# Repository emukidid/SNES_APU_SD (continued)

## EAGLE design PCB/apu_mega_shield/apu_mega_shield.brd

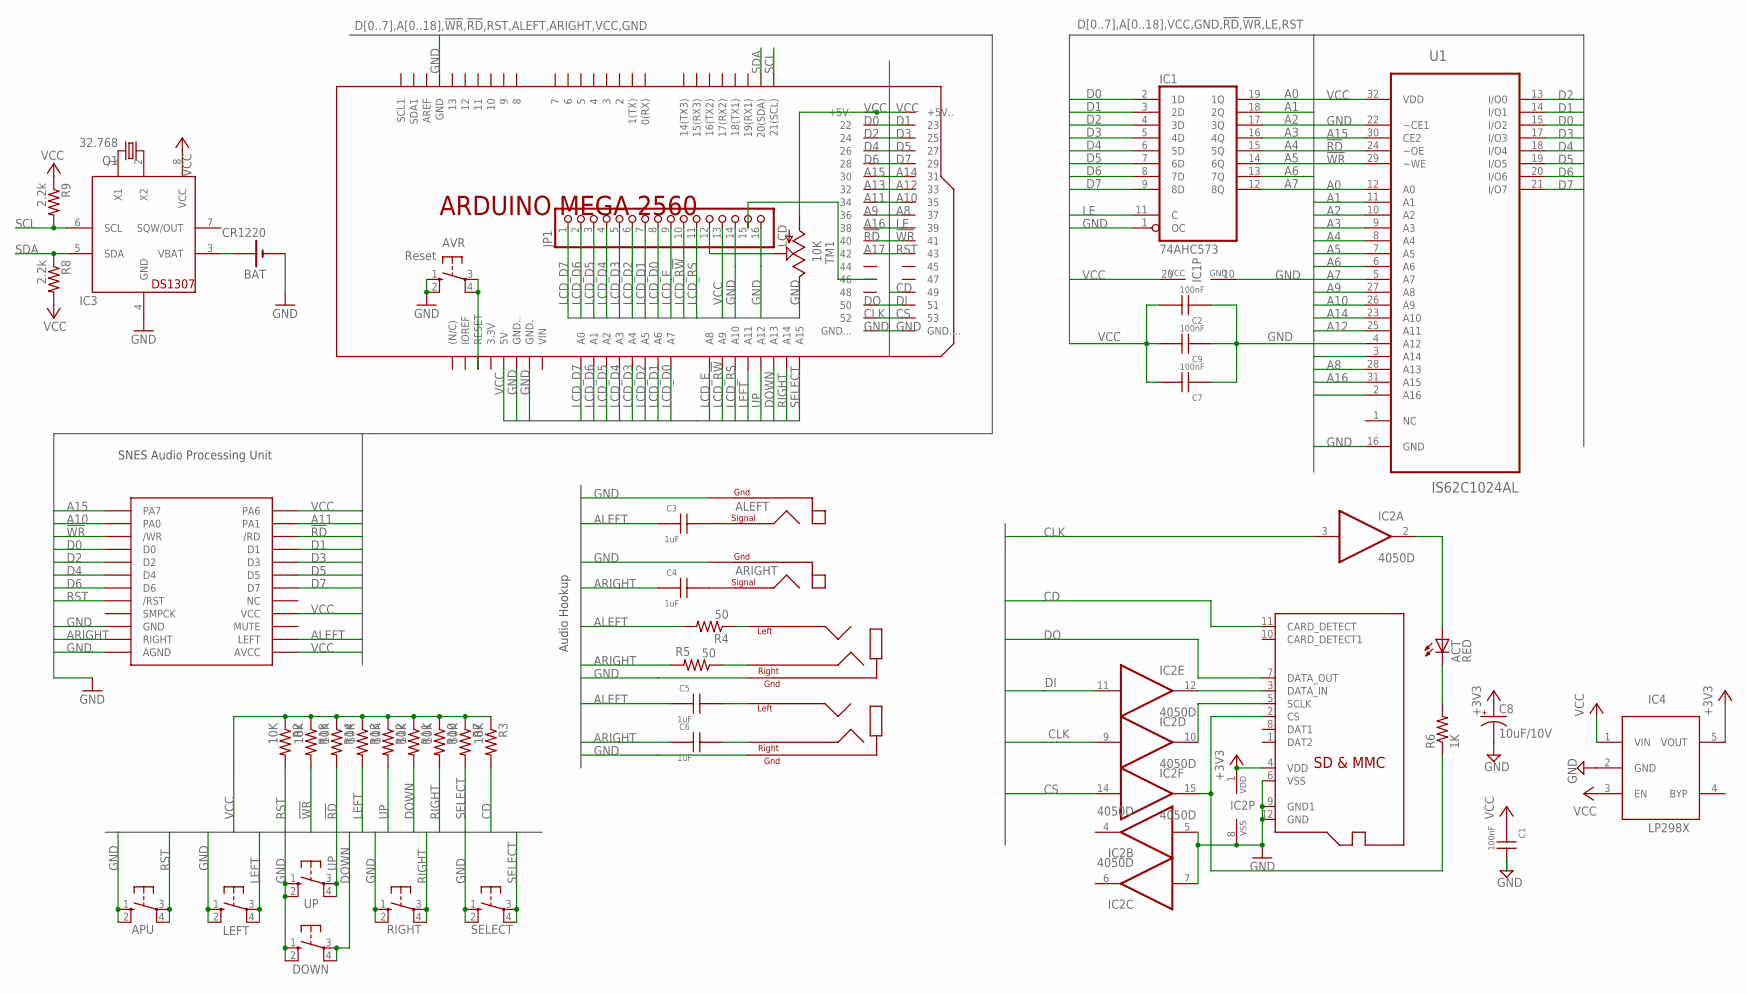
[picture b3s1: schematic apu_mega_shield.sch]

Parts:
ACT: RED; CHIP-LED0805
APU: Reset; B3F-10XX
AVR: Reset; B3F-10XX
BAT: CR1220; CR1220-SMD
C1, C2, C7, C9: 100nF; C0805
C3, C4, C5, C6: 1uF; C0805
C8: 10uF/10V; A/3216-18R
DOWN: 10-XX; B3F-10XX
IC1: 74AHC573; SO20W
IC2: 4050D; SO16
IC3: DS1307; SO-08
IC4: LP298XS; SOT23-5L
JP1: LCD; 1X16
LEFT: 10-XX; B3F-10XX
Q1: 32.768; SMD
R2, R3, R7, R10, R11, R12, R13, R14, R15: 10K; R0805
R4, R5: 50; R0805
R6: 1K; R0805
R8, R9: 2.2k; R0805
RIGHT: 10-XX; B3F-10XX
SELECT: 10-XX; B3F-10XX
TM1: 10K; CA6H
U1: IS62C1024AL; SOIC127P1412X305-32N
U$1: APU
U$2, U$3: HEADPHONE; SJ1-3533N
U$4, U$5: RCA; RCJ-01X
U$6: ARDUINO_MEGA_2560_LITENO_LABELS; ARDUINO_MEGA2560_LITE_NO_LABELS
UP: 10-XX; B3F-10XX
X1: MICROSDMOLEX; MICROSD-1

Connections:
!RD: R14.2, U1.24 (~OE), U$1.P$6 (/RD), U$6.40
!WR: R15.2, U1.29 (~WE), U$1.P$5 (/WR), U$6.41
+3V3: C8.+, IC2.1 (VDD), IC4.5 (VOUT), X1.4 (VDD)
A0: IC1.19 (1Q), U1.12 (A0)
A1: IC1.18 (2Q), U1.11 (A1)
A2: IC1.17 (3Q), U1.10 (A2)
A3: IC1.16 (4Q), U1.9 (A3)
A4: IC1.15 (5Q), U1.8 (A4)
A5: IC1.14 (6Q), U1.7 (A5)
A6: IC1.13 (7Q), U1.6 (A6)
A7: IC1.12 (8Q), U1.5 (A7)
A8: U1.28 (A13), U$6.37
A9: U1.27 (A8), U$6.36
A10: U1.26 (A9), U$1.P$3 (PA0), U$6.35
A11: U1.3 (A14), U$1.P$4 (PA1), U$6.34
A12: U1.25 (A11), U$6.33
A13: U1.4 (A12), U$6.32
A14: U1.23 (A10), U$6.31
A15: U1.30 (CE2), U$1.P$1 (PA7), U$6.30
A16: U1.31 (A15), U$6.38
A17: U1.2 (A16), U$6.42
ALEFT: C3.1, C5.1, R4.2, U$1.P$22 (LEFT)
ARIGHT: C4.1, C6.1, R5.2, U$1.P$21 (RIGHT)
BUF_CLK: IC2.10 (O), X1.5 (SCLK)
BUF_CS: IC2.15 (O), R6.1, X1.2 (CS)
BUF_DI: IC2.12 (O), X1.3 (DATA_IN)
BUF_LED: ACT.A, IC2.2 (O)
CD: R3.2, U$6.49, X1.11 (CARD_DETECT)
CLK: IC2.3 (I), IC2.9 (I), U$6.52
CS: IC2.14 (I), U$6.53
D0: IC1.2 (1D), U1.15 (I/O2), U$1.P$7 (D0), U$6.22
D1: IC1.3 (2D), U1.14 (I/O1), U$1.P$8 (D1), U$6.23
D2: IC1.4 (3D), U1.13 (I/O0), U$1.P$9 (D2), U$6.24
D3: IC1.5 (4D), U1.17 (I/O3), U$1.P$10 (D3), U$6.25
D4: IC1.6 (5D), U1.18 (I/O4), U$1.P$11 (D4), U$6.26
D5: IC1.7 (6D), U1.19 (I/O5), U$1.P$12 (D5), U$6.27
D6: IC1.8 (7D), U1.20 (I/O6), U$1.P$13 (D6), U$6.28
D7: IC1.9 (8D), U1.21 (I/O7), U$1.P$14 (D7), U$6.29
DI: IC2.11 (I), U$6.51
DO: U$6.50, X1.7 (DATA_OUT)
DOWN: DOWN.3, DOWN.4 (P1), R11.2, U$6.A13
GND: APU.1 (S), APU.2 (S1), AVR.1 (S), AVR.2 (S1), BAT.-, C1.2, C2.1, C7.1, C8.-, C9.1, DOWN.1 (S), DOWN.2 (S1), IC1.1 (OC), IC1.10 (GND), IC2.5 (I), IC2.7 (I), IC2.8 (VSS), IC3.4 (GND), IC4.2 (GND), JP1.14, JP1.16, LEFT.1 (S), LEFT.2 (S1), RIGHT.1 (S), RIGHT.2 (S1), SELECT.1 (S), SELECT.2 (S1), TM1.E, U1.16 (GND), U1.22 (~CE1), U$1.P$19 (GND), U$1.P$23 (AGND), U$2.GND, U$3.GND, U$4.PGND1, U$4.PGND2 (PGND1), U$4.PGND3 (PGND1), U$5.PGND1, U$5.PGND2 (PGND1), U$5.PGND3 (PGND1), U$6.GND, U$6.GND., U$6.GND.., U$6.GND..., U$6.GND...., UP.1 (S), UP.2 (S1), X1.6 (VSS), X1.9 (GND1), X1.12 (GND)
LCD_D0: JP1.8, U$6.A7
LCD_D1: JP1.7, U$6.A6
LCD_D2: JP1.6, U$6.A5
LCD_D3: JP1.5, U$6.A4
LCD_D4: JP1.4, U$6.A3
LCD_D5: JP1.3, U$6.A2
LCD_D6: JP1.2, U$6.A1
LCD_D7: JP1.1, U$6.A0
LCD_E: JP1.9, U$6.A8
LCD_R!W: JP1.10, U$6.A9
LCD_RS: JP1.11, U$6.A10
LE: IC1.11 (C), U$6.39
LEFT: LEFT.3, LEFT.4 (P1), R13.2, U$6.A11
unnamed: AVR.3, AVR.4 (P1), U$6.RESET
unnamed: C3.2, U$4.PSIG
unnamed: C4.2, U$5.PSIG
unnamed: C5.2, U$3.LEFT
unnamed: C6.2, U$3.RIGHT
unnamed: R4.1, U$2.LEFT
unnamed: R5.1, U$2.RIGHT
unnamed: ACT.C, R6.2
unnamed: JP1.12, TM1.S
unnamed: JP1.15, U$6.46
unnamed: BAT.+$1 (+), BAT.+$2 (+), IC3.3 (VBAT)
unnamed: IC3.1 (X1), Q1.2
unnamed: IC3.2 (X2), Q1.1
RIGHT: R10.2, RIGHT.3, RIGHT.4 (P1), U$6.A14
RST: APU.3, APU.4 (P1), R2.2, U$1.P$15 (/RST), U$6.43
SCL: IC3.6 (SCL), R9.2, U$6.21 (21(SCL))
SDA: IC3.5 (SDA), R8.1, U$6.20 (20(SDA))
SELECT: R7.2, SELECT.3, SELECT.4 (P1), U$6.A15
UP: R12.2, U$6.A12, UP.3, UP.4 (P1)
VCC: C1.1, C2.2, C7.2, C9.2, IC1.20 (VCC), IC3.8 (VCC), IC4.1 (VIN), IC4.3 (EN), JP1.13, R2.1, R3.1, R7.1, R8.2, R9.1, R10.1, R11.1, R12.1, R13.1, R14.1, R15.1, TM1.A, U1.32 (VDD), U$1.P$2 (PA6), U$1.P$18 (VCC), U$1.P$24 (AVCC), U$6.5V, U$6.5V. (+5V.), U$6.5V.. (+5V..)

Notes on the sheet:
SNES Audio Processing Unit
Audio Hookup

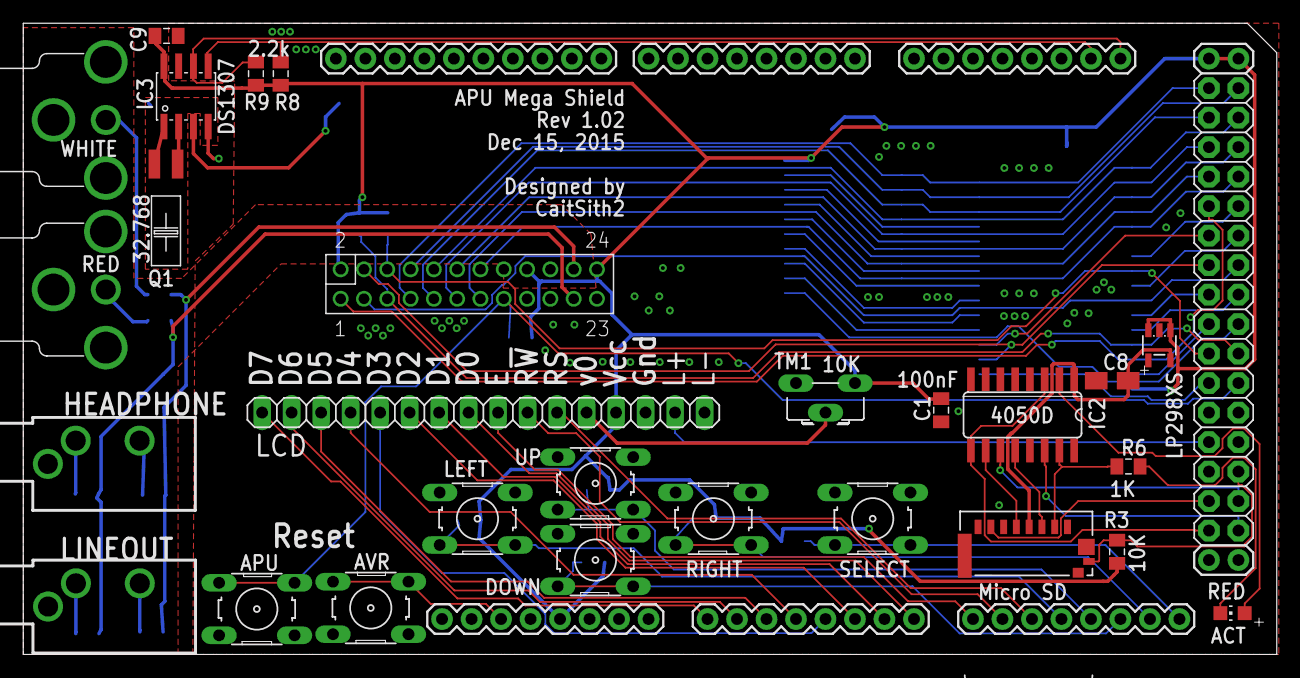
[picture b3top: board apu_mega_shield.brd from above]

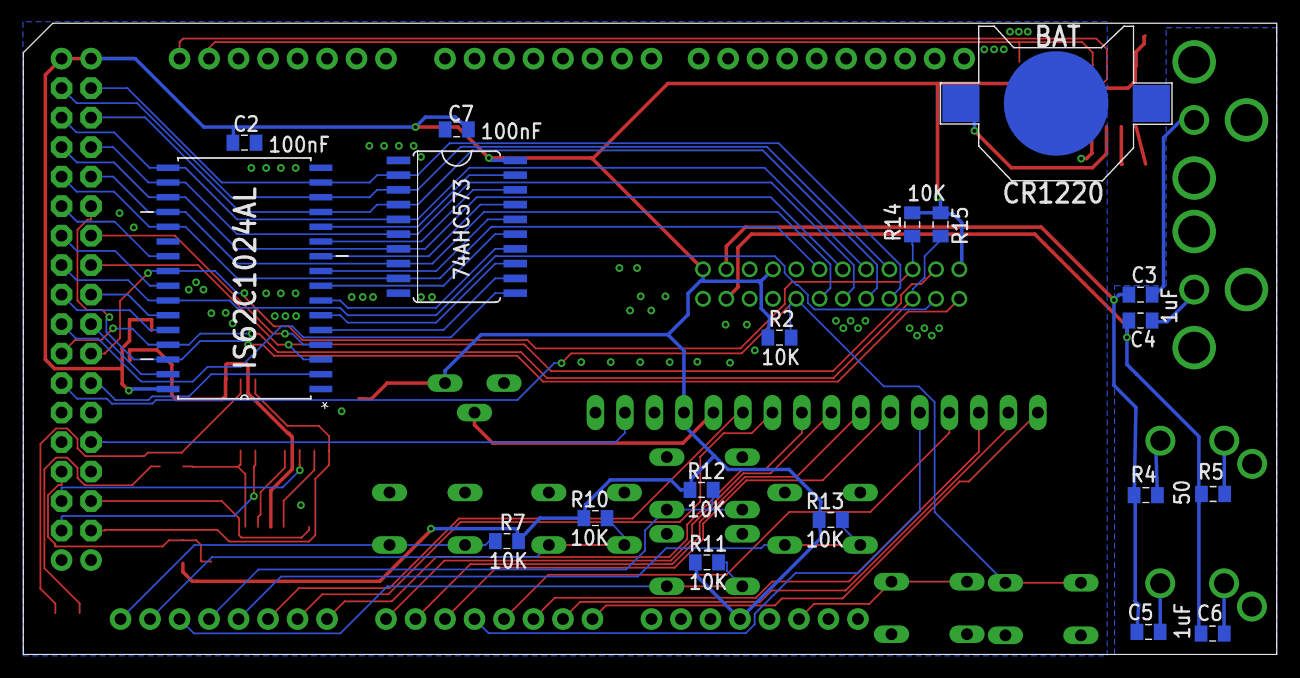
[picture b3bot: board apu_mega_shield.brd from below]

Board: 2 copper layers, 108.0 x 54.4 mm, 47 parts (19 on the bottom side), 75 nets.

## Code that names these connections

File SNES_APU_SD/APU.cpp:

#include "APU.h"

#include <inttypes.h>
#include "Arduino.h"

APU::APU()
{
  init(APU_TYPE_XMEM);
}

APU::APU(uint8_t type)
{
  init(type);
}

void APU::init(uint8_t type)
{
#if not (defined(__AVR_ATmega2560__) || defined(__AVR_ATmega1280__))
  PORTB = 0x0F;
  DDRB = 0x0F;
  DDRC &= 0xC0;
  PORTC &= 0xC0;
   
#else
  mega_type = type;
  if (mega_type)
    init_mega_xmem();
  else
    init_mega();
#endif
}

#if (defined(__AVR_ATmega2560__) || defined(__AVR_ATmega1280__))
void APU::init_mega()
{
  PORTH = 0x60;
  DDRH = 0x03;  //Digital pins 8-9. (A0,A1)
  PORTB = 0x30;
  DDRB |= 0x30;  //Digital pins 10-11 (/RD,/WR)
  DDRF = 0x00; 
  PORTF = 0x00; //Analog Pin 0 (/RESET)
  
}

int APU::init_mega_xmem()
{
  XMCRB = 0;
  XMCRA = (1<<SRE)  //Enable Xmem Interface
        | (1 << SRL2) | (0 << SRL1) | (0 << SRL0) //Set upper sector limit
        | (0 << SRW11) | (0 << SRW10) //Set upper sector wait-states
        | (0 << SRW01) | (0 << SRW00); //Set lower sector wait-states.
  //SRE - Enable XMem Interface
  //SRL2 = 1, SRL1 = 0, SRL0 = 0 - Lower sector = 0x2200-0x7FFF, Upper sector = 0x8000-0xFFFF
  //SRWx1 = 0, SRWx0 = 0 - No wait-states
  //SRWx1 = 0, SRWx0 = 1 - Wait one cycle during read/write strobe
  //SRWx1 = 1, SRWx0 = 0 - Wait two cycles during read/write strobe
  //SRWx1 = 1, SRWx0 = 1 -      And wait one cycle before driving out new address.

  DDRC = 0xFF;
  PORTC = 0x00;
  XMCRB = (0 << XMBK) // External Memory Bus-keeper enable
        | (0 << XMM2) | (0 << XMM1) | (0 << XMM0); //External Memory High Mask

  // XMM2 XMM1 XMM0 - Released IO pins (Arduino notation, AVR notation)
  // 0    0    0    - None
  // 0    0    1    - 30   , PC7
  // 0    1    0    - 30-31, PC6-PC7
  // 0    1    1    - 30-32, PC5-PC7
  // 1    0    0    - 30-33, PC4-PC7
  // 1    0    1    - 30-34, PC3-PC7
  // 1    1    0    - 30-35, PC2-PC7
  // 1    1    1    - 30-37, PC0-PC7

  
  PORTL |= 0x80; //additional address lines
  DDRL |= 0x80;
  DDRL &= 0xBF; //Reset Line
  PORTL &= 0xBF;
  
  DDRD |= 0x80; //Additional address lines
}



#endif

uint8_t APU::read(uint8_t address)
{
  #if not (defined(__AVR_ATmega2560__) || defined(__AVR_ATmega1280__))
    return read_arduino(address);
  #else
    if(!mega_type)
      return read_arduino_mega(address);
    else
      return read_arduino_mega_xmem(address);
  #endif
}

void APU::write(uint8_t address, uint8_t data)
{
  #if not (defined(__AVR_ATmega2560__) || defined(__AVR_ATmega1280__))
    write_arduino(address, data);
  #else
    if(!mega_type)
      write_arduino_mega(address, data);
    else
      write_arduino_mega_xmem(address, data);
  #endif
}


void APU::reset()
{
  #if not (defined(__AVR_ATmega2560__) || defined(__AVR_ATmega1280__))
    reset_arduino();
  #else
    if(!mega_type)
      reset_arduino_mega();
    else
      reset_arduino_mega_xmem();
  #endif
}

#if not (defined(__AVR_ATmega2560__) || defined(__AVR_ATmega1280__))
uint8_t APU::read_arduino(uint8_t address)
{
  unsigned char data;

  DDRB = 0x0F;
  DDRD &= ~0xFC;
  PORTB &= ~0x03;
  PORTB |= (address & 0x03);

  PORTB &= ~0x04;
  __asm__ __volatile__ ("nop");
  __asm__ __volatile__ ("nop");
  data=((PINB&0x30)>>4) | (PIND&0xFC);
  PORTB |= 0x04;
  return data;
}



void APU::write_arduino(uint8_t address, uint8_t data)
{
  DDRB = 0x3F;
  DDRD |= 0xFC;

  PORTD &= ~0xFC;
  PORTD |= (data & 0xFC);

  PORTB &= ~0x33;
  PORTB |= (address & 0x03);
  PORTB |= ((data & 0x03)<<4);
  PORTB &= ~0x08;
  __asm__ __volatile__ ("nop");
  __asm__ __volatile__ ("nop");
  PORTB |= 0x08;
}

void APU::reset_arduino()
{
  pinMode(RESET_PIN,OUTPUT);
  pinMode(RESET_PIN,INPUT);
}
#else
uint8_t APU::read_arduino_mega(uint8_t address)
{
  unsigned char data = 0;
  DDRB |= 0x30;    //APU RD/WR
  DDRH |= 0x60;    //APU A0-A1
  DDRB &= ~0xC0;  //APU D0-D1
  DDRE &= ~0x38;  //APU D2-D3, D5
  DDRG &= ~0x20;  //APU D4
  DDRH &= ~0x18;  //APU D6-D7
  PORTH &= ~0x60;
  PORTH |= ((address & 0x03)<<5);

  PORTB &= ~0x10;
  __asm__ __volatile__ ("nop");
  __asm__ __volatile__ ("nop");
  data=((PINB&0xC0)>>6) | ((PINE&0x30)>>2) | ((PING&0x20)>>1) | ((PINE&0x08)<<2) | ((PINH&0x18)<<3);
  PORTB |= 0x10;
  return data;
}

void APU::write_arduino_mega(uint8_t address, uint8_t data)
{
  DDRB |= 0xF0;   //APU RD/WR,  D0-D1
  DDRE |= 0x38;   //APU D2-D3, D5
  DDRG |= 0x20;   //APU D4
  DDRH |= 0x18;   //APU D6-D7

  PORTB &= ~0xC0;
  PORTB |= ((data & 0x03)<<6);
  
  PORTE &= ~0x38;
  PORTE |= ((data & 0x0C)<<2) | ((data & 0x20)>>2);
  
  PORTG &= ~0x20;
  PORTG |= ((data&0x10)<<1);
  
  PORTH &= ~0x78;
  PORTH |= ((address & 0x03)<<5) | ((data&0xC0)>>3);
  
  PORTB &= ~0x20;
  __asm__ __volatile__ ("nop");
  __asm__ __volatile__ ("nop");
  PORTB |= 0x20;
}

void APU::reset_arduino_mega()
{
  pinMode(RESET_PIN_0,OUTPUT);
  pinMode(RESET_PIN_0,INPUT);
}

uint8_t APU::read_arduino_mega_xmem(uint8_t address)
{
  return _SFR_MEM8(0x2200 + ((address & 3) << 10));
}

void APU::write_arduino_mega_xmem(uint8_t address, uint8_t data)
{
  _SFR_MEM8(0x2200 + ((address & 3) << 10)) = data;
}

void APU::reset_arduino_mega_xmem()
{
  pinMode(RESET_PIN_1,OUTPUT);
  pinMode(RESET_PIN_1,INPUT);
}
#endif

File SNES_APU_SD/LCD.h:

#ifndef LiquidCrystal_h
#define LiquidCrystal_h
#if (defined(__AVR_ATmega2560__) || defined(__AVR_ATmega1280__))

#include <inttypes.h>
#include "Print.h"

// commands
#define LCD_CLEARDISPLAY 0x01
#define LCD_RETURNHOME 0x02
#define LCD_ENTRYMODESET 0x04
#define LCD_DISPLAYCONTROL 0x08
#define LCD_CURSORSHIFT 0x10
#define LCD_FUNCTIONSET 0x20
#define LCD_SETCGRAMADDR 0x40
#define LCD_SETDDRAMADDR 0x80

// flags for display entry mode
#define LCD_ENTRYRIGHT 0x00
#define LCD_ENTRYLEFT 0x02
#define LCD_ENTRYSHIFTINCREMENT 0x01
#define LCD_ENTRYSHIFTDECREMENT 0x00

// flags for display on/off control
#define LCD_DISPLAYON 0x04
#define LCD_DISPLAYOFF 0x00
#define LCD_CURSORON 0x02
#define LCD_CURSOROFF 0x00
#define LCD_BLINKON 0x01
#define LCD_BLINKOFF 0x00

// flags for display/cursor shift
#define LCD_DISPLAYMOVE 0x08
#define LCD_CURSORMOVE 0x00
#define LCD_MOVERIGHT 0x04
#define LCD_MOVELEFT 0x00

// flags for function set
#define LCD_8BITMODE 0x10
#define LCD_4BITMODE 0x00
#define LCD_2LINE 0x08
#define LCD_1LINE 0x00
#define LCD_5x10DOTS 0x04
#define LCD_5x8DOTS 0x00

// Control line pins
#define LCD_E 0x01
#define LCD_RW 0x02
#define LCD_RS 0x04

class LiquidCrystal : public Print {
public:
  LiquidCrystal();

  void init();
    
  void begin(uint8_t cols, uint8_t rows, uint8_t charsize = LCD_5x8DOTS);

  void clear();
  void home();

  void noDisplay();
  void display();
  void noBlink();
  void blink();
  void noCursor();
  void cursor();
  void scrollDisplayLeft();
  void scrollDisplayRight();
  void leftToRight();
  void rightToLeft();
  void autoscroll();
  void noAutoscroll();

  void setRowOffsets(int row1, int row2, int row3, int row4);
  void createChar(uint8_t, uint8_t[]);
  void setCursor(uint8_t, uint8_t); 
  virtual size_t write(uint8_t);
  void command(uint8_t);
  
  using Print::write;
private:
  void send(uint8_t, uint8_t);
  void write8bits(uint8_t);
  void pulseEnable();

  uint8_t _rs_pin; // LOW: command.  HIGH: character.
  uint8_t _rw_pin; // LOW: write to LCD.  HIGH: read from LCD.
  uint8_t _enable_pin; // activated by a HIGH pulse.
  uint8_t _data_pins[8];

  uint8_t _displayfunction;
  uint8_t _displaycontrol;
  uint8_t _displaymode;

  uint8_t _initialized;

  uint8_t _numlines;
  uint8_t _row_offsets[4];
};

#endif
#endif

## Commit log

2015-10-27 - Initial commit
2015-10-27 Initial commit (Not yet ready for production.)
2015-10-27 Micro SD card detect pullup resistor added.
2015-10-27 Removed the OR gate reset mechanism, as that pretty much was only used on Arduino / Parallel port hybrid builds.
2015-10-27 Part list for the Arduino mega apu shield PCB
2015-10-27 Rename apu_mega_shield.brd to PCB/apu_mega_shield.brd
2015-10-27 Rename apu_mega_shield.sch to PCB/apu_mega_shield.sch
2015-10-28 Added 3.3v regulator due to Arduino 3.3v line being limited to 50ma. (Micro SD cards can draw up to 100ma while they are being written to.)
2015-10-28 PC loading code restored. :)
2015-10-28 Apuplay PC spc loader added.
2015-10-28 Remove files that were not supposed to versioned in the first place.
2015-10-28 Added .gitignore
2015-10-28 Binary build.
2015-10-29 LCD now interfaced using 8-bit mode instead of 4-bit mode.
2015-10-29 Modified the standard LCD library, for speed, and to match with the mega shield design.
2015-10-29 PC interface now uploads at 250,000 bps. :)
2015-10-29 115200 baud fallback added for backwards compatibility with legacy arduino sketches.
2015-10-29 Commented some of the code. Reduced the delay from when the string is printed, to when the arduino attempts to load file.spc from the SD card. (2 seconds of every arduino reset is occupied in the ard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
2015-10-29 Removed an unnecessary delay(250); from the upload spc block.
2015-10-30 Hopefully final PCB design for version 1.0 :)
2015-10-30 Changed silkscreen widths. Added gerbers for ordering at places that don't support eagle files directly. :)
2015-10-31 Replaced Capacitors C3,C4,C5,C6 with parts that are a bit cheaper.
2015-10-31 Parts list made into csv format.
2015-10-31 Removed quote marks.
2015-10-31 Sketch now works, (in PC mode only), on the standard Arduino formfactor boards.
2015-10-31 Updated the binary to latest
2015-11-01 Bill of Materials updated with a female header that should be long enough to mate with the long male pins.
2015-11-01 Cleaned up a redundant net connection point.
2015-11-02 minor bug fix for when certain buttons are accidentally double-clicked.
2015-11-02 Rename APU.cpp to SNES_APU_SD/APU.cpp
2015-11-02 Rename APU.h to SNES_APU_SD/APU.h
2015-11-02 Rename LCD.cpp to SNES_APU_SD/LCD.cpp
2015-11-02 Rename LCD.h to SNES_APU_SD/LCD.h
2015-11-02 Rename SNES_APU_SD.ino to SNES_APU_SD/SNES_APU_SD.ino
2015-11-03 Added preliminary spc2 file support. (still hard-coded filename).
    Fixed a minor bug in the bootcode seaching function.
2015-11-04 created an spc file open function.
2015-11-08 spc2 file spec now supports upload mask. Implemented into the PC player. spc2 file bootcode now chosen only in automatic freespace search mode. (freespacesearch = 0).
2015-11-08 Commented the boot code and dsp loader blocks with a disassembly. Planning on changing both of them, so that the boot loader block can be made smaller than the 77 bytes it currently is. :)
2015-11-13 Improved the final spc uploading bootcode, made 30 bytes smaller.
2015-11-16 xmem interface added.
2015-11-16 PCB design for mounting APU components taken from a revision 2 snes.
2015-11-16 Improvements on the pc application
2015-11-18 Tweaks to the Tales of Phantasia / Star Ocean Audio control panel.
2015-11-18 All parts that are not buttons or connectors replaced with SMT equivalents. :)
2015-11-19 Integrated APU mega shield
2015-11-19 Forgot a couple of parts
2015-11-24 R1 removed from PCB. It was supposed to be the current limiting resistor for the LCD backlight, however, the LCD module in use already has a current limiting resistor mounted right on that module.
2015-11-25 Tweaked reset button layouts. On the module version of the board, SD card connector and its supporting components moved.
2015-11-25 Boot code location, and upload time now reported in status bar.
2015-11-27 Optimized layout a bit more.
2015-12-15 Final revisions to the PCB design, hopefully. :)
2015-12-23 Reorganize directory structure
2015-12-23 Bill of materials added for hardware SPC player
2015-12-23 Changes to help emu_kidid debug his setup.
2015-12-23 schematic sheets used more effectively.
2015-12-23 one last debugging related change.
2015-12-23 Missed a part out of the BOM
2015-12-23 Change out PTC fuse for better clearance.
2015-12-24 Added in a clock prescaler adjustment option.
2015-12-24 minor fix to swapped out component on schematic.
2015-12-24 eagle project description
2016-01-05 - Fix overflow with last SPC block read
2016-03-04 Basic directory navigation. put all folders containing spc files inside of the folder named dir/
2016-03-05 Implemented LCD display scrolling. Tweaked the UI controls for directory navigation and SPC playing.
2016-03-05 More LCD tweaking
2016-03-05 Implemented basic RTC mode. SPC now caches to SRAM, and is manipulated from there.
2016-03-05 Prescaler now set to zero for everything except SPC loading. Prescaler of 1 used for SPC loading.
2016-03-06 Converted as many of the constant strings to be stored into strictly flash memory as possible. Cleaned up code now that data is loaded into the 128KB sram.
2016-03-06 RTC now refreshes about once per second.
2016-03-07 LCD now shows spc upload progress when an spc is uploading to the APU.
2016-03-07 minor tweak.
2016-03-14 PC Side communications
    Added various commands for a planned total rewrite of the PC side
    client,.
2016-03-15 Changed micro-SD holder to push-in-push-out type.
2016-03-15 Whoops, wrong microSD holder.
2016-03-25 Auto playback mode added
2016-03-25 APU reset after last file in directory is played.
2016-03-26 Holding reset button no longer exceeds max rated IO line current.
2016-03-26 Added Auto play stop, and Next/Prev song.
2016-03-27 fixed legacy arduino compilation once again.
2016-04-04 Currently playing song scroller and time remaining.
2016-04-04 APU reset button now has a 470 ohm series resistor to ground.
2016-04-04 few more bug fixes
2016-04-08 Tweaked tag storage size to use less ram.
2016-04-08 Lots of tweaks. Really should commit changes more often.
2016-04-11 PC Client related changes
2016-04-12 File depth related code now a #define.
2016-04-12 File depth error handling. Current file bug fixed.
2016-04-13 More tag related output
2016-04-13 APU Play Mega client initial commit
2016-04-13 More text output on certain events.
2016-04-13 Tweaked the tag layout
2016-04-13 Directory entry handling code now made more responsive.
2016-07-22 minor tweaks
2019-02-26 - Change upload progress indication on LCD - Sequential play by default, hold right to play one track forever - Display when endless play is on with "R" after time on LCD
2025-09-21 Root directory now named "spc" to match with the Analogue Super NT.
